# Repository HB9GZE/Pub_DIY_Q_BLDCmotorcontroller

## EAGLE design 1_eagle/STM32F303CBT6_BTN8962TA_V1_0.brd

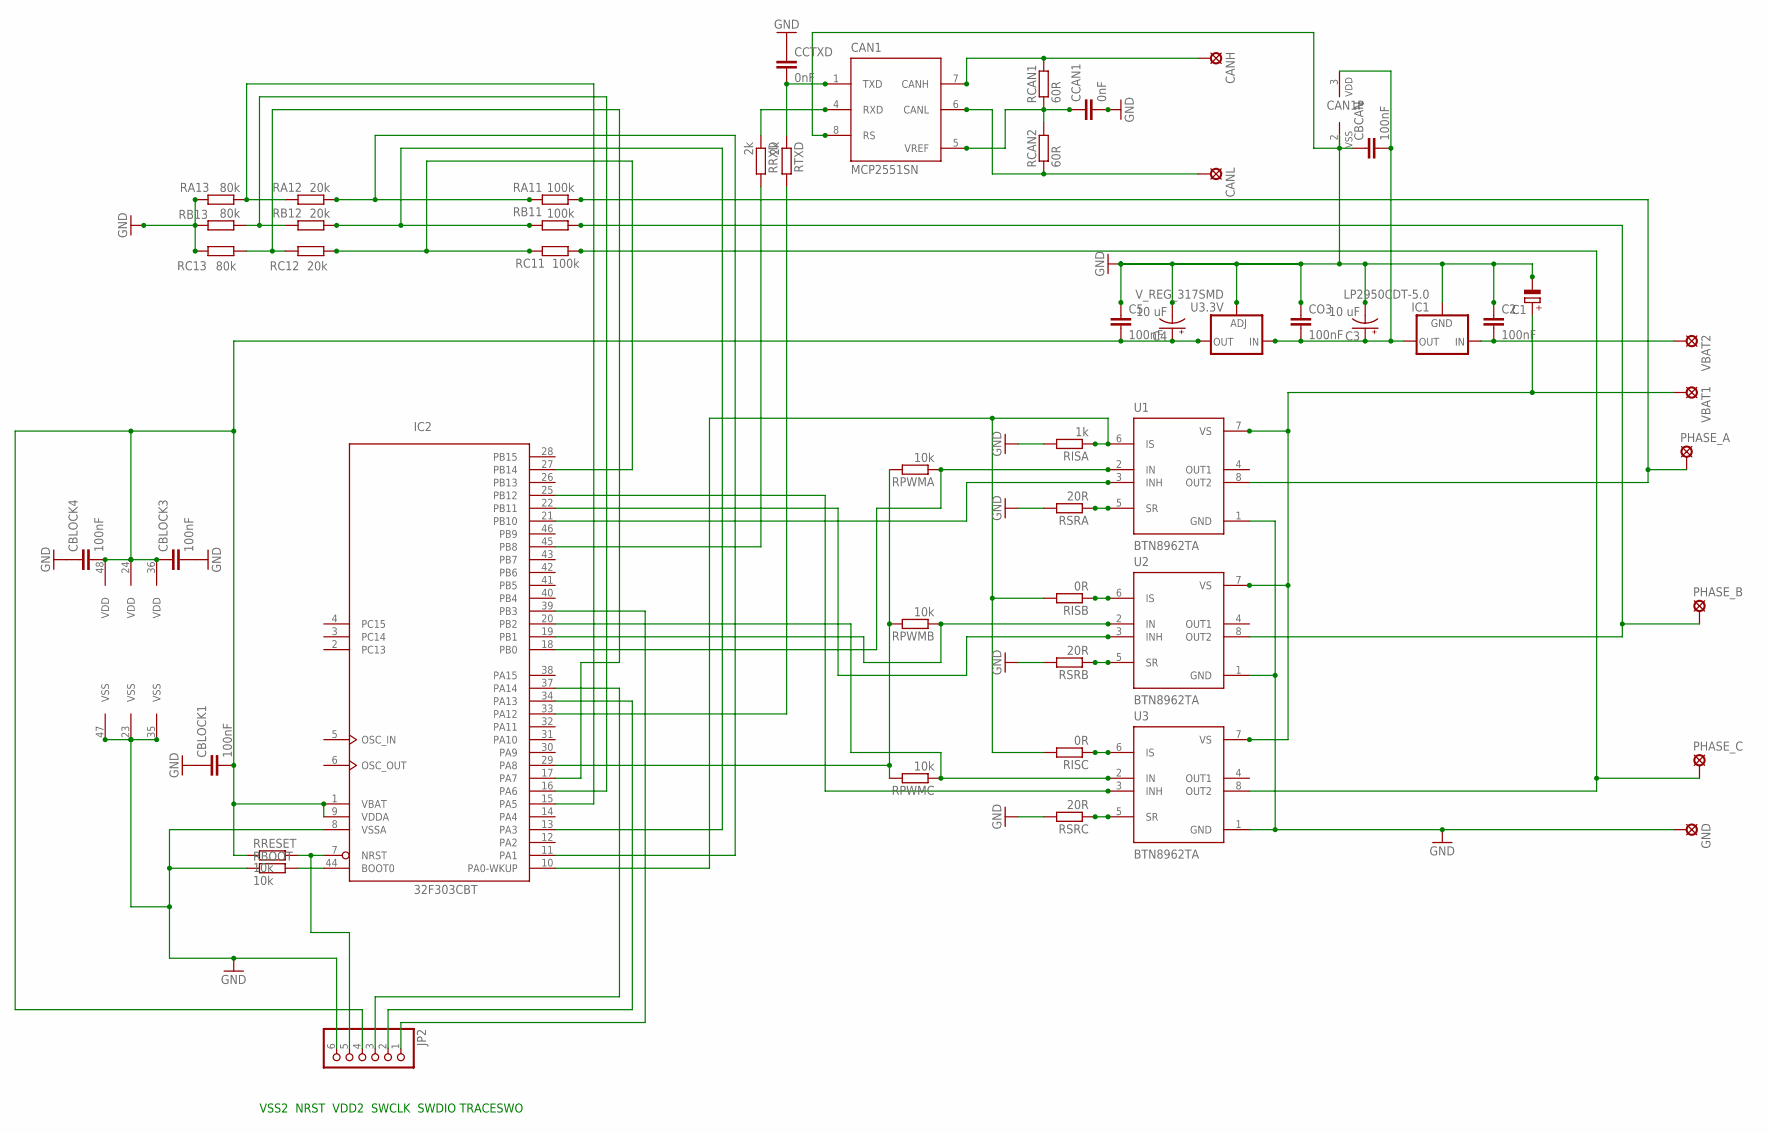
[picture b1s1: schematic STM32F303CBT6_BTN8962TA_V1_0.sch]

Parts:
C1: CPOL-EUE3.5-10; E3,5-10
C2, C5: 100nF; C0805
C3, C4: 10 uF; PANASONIC_D
CAN1: MCP2551SN; SO-08
CANH: LSP10
CANL: LSP10
CBCAN: 100nF; C0805
CBLOCK1, CBLOCK3, CBLOCK4: 100nF; C0805
CCAN1: 0nF; C0805
CCTXD: 0nF; C0805
CO3: 100nF; C0805
GND: SE14
IC1: LP2950CDT-5.0; DPACK
IC2: 32F303CBT; LQFP48
JP2: PINHD-1X6; 1X06
PHASE_A: SE14
PHASE_B: SE14
PHASE_C: SE14
RA11: 100k; R0805
RA12: 20k; R0805
RA13: 80k; R0805
RB11: 100k; R0805
RB12: 20k; R0805
RB13: 80k; R0805
RBOOT: 10k; R0805
RC11: 100k; R0805
RC12: 20k; R0805
RC13: 80k; R0805
RCAN1, RCAN2: 60R; R0805
RISA: 1k; R0805
RISB: 0R; R0805
RISC: 0R; R0805
RPWMA: 10k; R0805
RPWMB: 10k; R0805
RPWMC: 10k; R0805
RRESET: 10k; R0805
RRXD: 2k; R0805
RSRA: 20R; R0805
RSRB: 20R; R0805
RSRC: 20R; R0805
RTXD: 2k; R0805
U1, U2, U3: BTN8962TA; TO127P1500X440-8N-1
U3.3V: V_REG_317SMD; SOT223
VBAT1, VBAT2: SE14

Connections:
A: IC2.11 (PA1), RA11.2, RA12.1
B: IC2.13 (PA3), RB11.2, RB12.1
C: IC2.27 (PB14), RC11.2, RC12.1
GND: C1.-, C2.1, C3.-, C4.-, C5.1, CAN1.2 (VSS), CAN1.8 (RS), CBCAN.1, CBLOCK1.1, CBLOCK3.2, CBLOCK4.1, CCAN1.2, CCTXD.1, CO3.1, GND.MP, IC1.4 (GND), IC2.8 (VSSA), IC2.23 (VSS), IC2.35 (VSS), IC2.47 (VSS), JP2.6, RA13.2, RB13.2, RBOOT.1, RC13.2, RISA.2, RSRA.2, RSRB.2, RSRC.2, U1.1 (GND), U2.1 (GND), U3.1 (GND), U3.3V.1 (ADJ)
unnamed: PHASE_A.MP, RA11.1, U1.8 (OUT2)
unnamed: PHASE_B.MP, RB11.1, U2.8 (OUT2)
unnamed: PHASE_C.MP, RC11.1, U3.8 (OUT2)
unnamed: C1.+, U1.7 (VS), U2.7 (VS), U3.7 (VS), VBAT1.MP
unnamed: IC2.45 (PB8), RRXD.2
unnamed: RSRA.1, U1.5 (SR)
unnamed: RISB.1, U2.6 (IS)
unnamed: RSRB.1, U2.5 (SR)
unnamed: RISC.1, U3.6 (IS)
unnamed: IC2.10 (PA0-WKUP), RISA.1, RISB.2, RISC.2, U1.6 (IS)
unnamed: RSRC.1, U3.5 (SR)
unnamed: IC2.39 (PB3), JP2.1
unnamed: IC2.19 (PB1), RPWMB.1, U2.2 (IN)
unnamed: IC2.20 (PB2), RPWMC.1, U3.2 (IN)
unnamed: IC2.25 (PB12), U3.3 (INH)
unnamed: IC2.29 (PA8), RPWMA.2, RPWMB.2, RPWMC.2
unnamed: IC2.22 (PB11), U2.3 (INH)
unnamed: IC2.21 (PB10), U1.3 (INH)
unnamed: IC2.18 (PB0), RPWMA.1, U1.2 (IN)
unnamed: IC2.34 (PA13), JP2.2
unnamed: IC2.37 (PA14), JP2.3
unnamed: IC2.33 (PA12), RTXD.2
unnamed: CAN1.4 (RXD), RRXD.1
unnamed: CAN1.6 (CANL), CANL.MP, RCAN2.1
unnamed: CAN1.1 (TXD), CCTXD.2, RTXD.1
unnamed: CAN1.5 (VREF), CCAN1.1, RCAN1.1, RCAN2.2
unnamed: IC2.44 (BOOT0), RBOOT.2
unnamed: C2.2, IC1.1 (IN), VBAT2.MP
unnamed: CAN1.7 (CANH), CANH.MP, RCAN1.2
unnamed: IC2.17 (PA7), RC12.2, RC13.1
unnamed: IC2.16 (PA6), RB12.2, RB13.1
unnamed: IC2.15 (PA5), RA12.2, RA13.1
unnamed: IC2.7 (NRST), JP2.5, RRESET.2
V50: C3.+, CAN1.3 (VDD), CBCAN.2, CO3.2, IC1.3 (OUT), U3.3V.3 (IN)
VDD: C4.+, C5.2, CBLOCK1.2, CBLOCK3.1, CBLOCK4.2, IC2.1 (VBAT), IC2.9 (VDDA), IC2.24 (VDD), IC2.36 (VDD), IC2.48 (VDD), JP2.4, RRESET.1, U3.3V.2 (OUT)

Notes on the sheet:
VSS2 NRST VDD2 SWCLK SWDIO TRACESWO

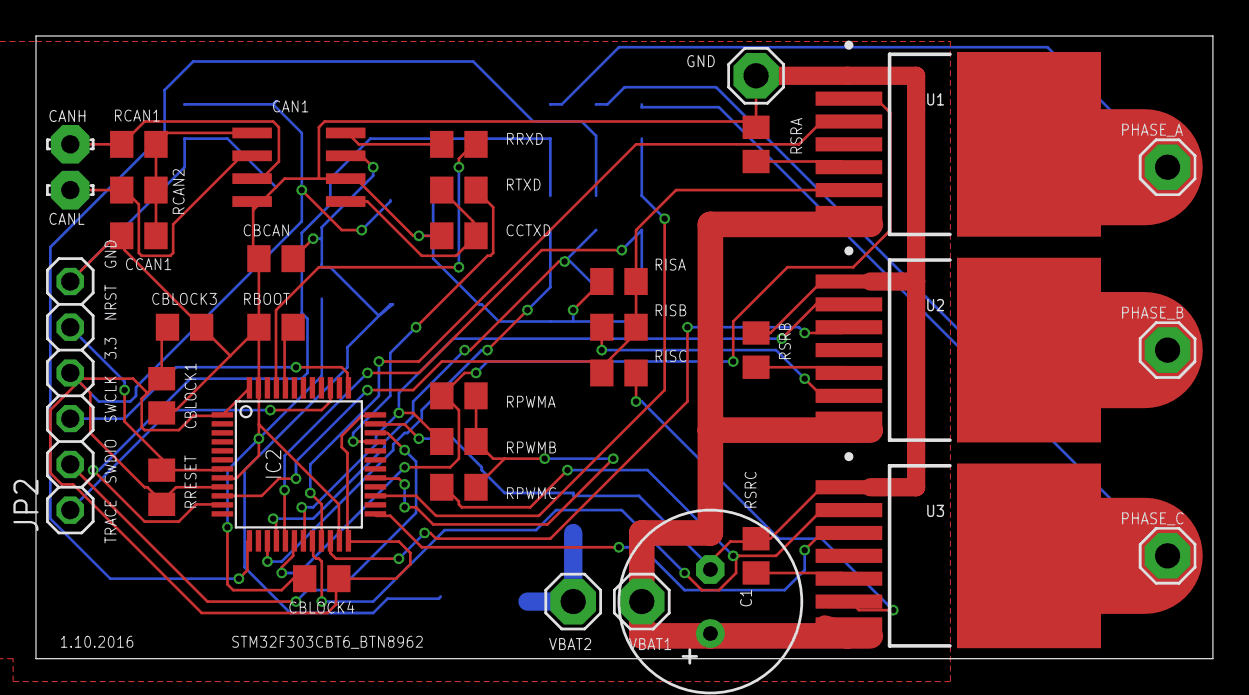
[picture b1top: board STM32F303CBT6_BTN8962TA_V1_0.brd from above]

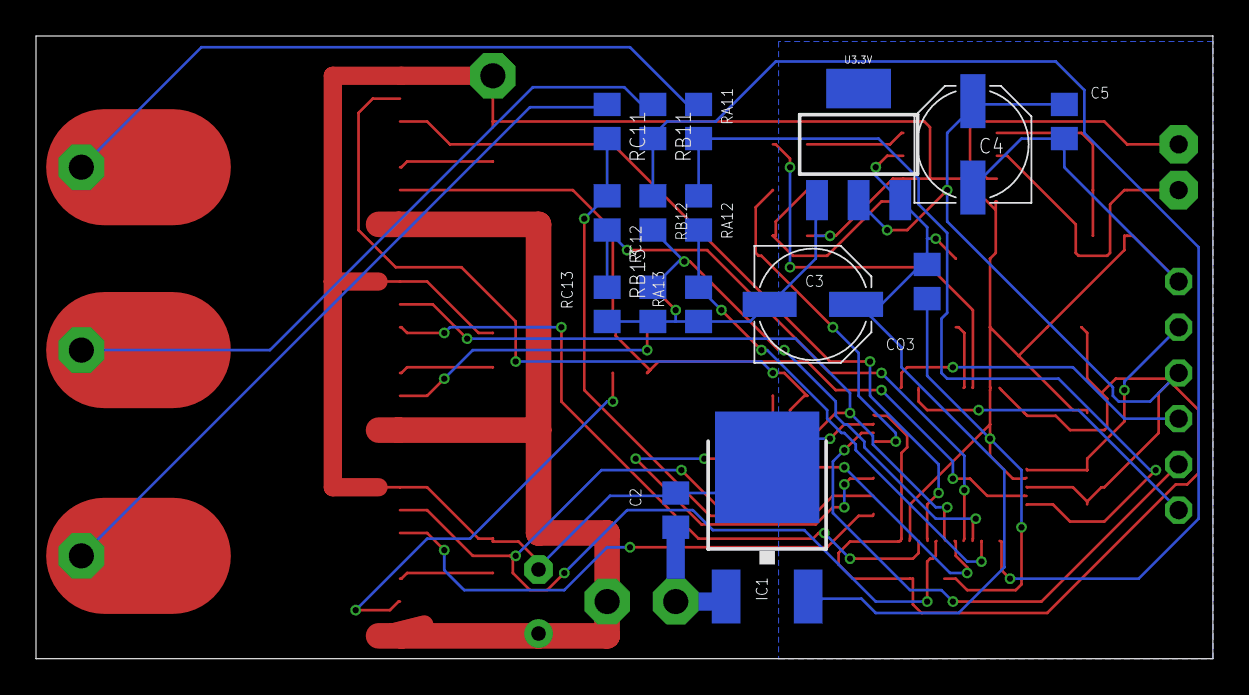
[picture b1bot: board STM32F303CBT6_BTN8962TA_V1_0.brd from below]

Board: 2 copper layers, 65.4 x 34.6 mm, 52 parts (16 on the bottom side), 39 nets.

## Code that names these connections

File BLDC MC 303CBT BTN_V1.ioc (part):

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Mcu.Name=STM32F303C(B-C)Tx
Mcu.Package=LQFP48
Mcu.UserName=STM32F303CBTx
PA0.Mode=IN1-Single-Ended
PA0.Signal=ADC1_IN1
PA1.Mode=INP
PA1.Signal=COMP1_INP
PA12.Mode=Master
PA12.Signal=CAN_TX
PA13.Mode=Trace_Asynchronous_SW
PA13.Signal=SYS_JTMS-SWDIO
PA14.Mode=Trace_Asynchronous_SW
PA14.Signal=SYS_JTCK-SWCLK
PA3.Mode=INP
PA3.Signal=COMP2_INP
PA4.Signal=COMP_DAC1_group
PA5.Signal=GPIO_Input
PA6.Signal=GPIO_Input
PA7.Signal=GPIO_Input
PA8.GPIOParameters=GPIO_Speed,GPIO_PuPd
PA8.GPIO_PuPd=GPIO_PULLDOWN
PA8.GPIO_Speed=GPIO_SPEED_FREQ_MEDIUM
PA8.Signal=S_TIM1_CH1
PB0.Signal=GPIO_Input
PB1.Signal=GPIO_Input
PB10.Signal=GPIO_Output
PB11.Signal=GPIO_Output
PB12.Signal=GPIO_Output
PB14.Mode=INP
PB14.Signal=COMP3_INP
PB2.Signal=GPIO_Input
PB3.Mode=Trace_Asynchronous_SW
PB3.Signal=SYS_JTDO-TRACESWO
PB8.Mode=Master
PB8.Signal=CAN_RX
RCC.HSEPLLFreq_Value=8000000
RCC.HSE_VALUE=8000000
RCC.SYSCLKFreq_VALUE=64000000
RCC.SYSCLKSourceVirtual=RCC_SYSCLKSOURCE_PLLCLK
board=BLDC MC 303CBT BTN_V1

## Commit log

2017-02-23 added comments
2017-02-23 added eagle files...
2017-04-03 version of first flight
2017-08-07 tune BLDC motor controller for faster response...
2017-08-09 new eagle files

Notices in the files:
parts and their libraries:
SparkFun-Capacitors: Licensing: CC v3.0 Share-Alike You are welcome to use this library for commercial purposes.
